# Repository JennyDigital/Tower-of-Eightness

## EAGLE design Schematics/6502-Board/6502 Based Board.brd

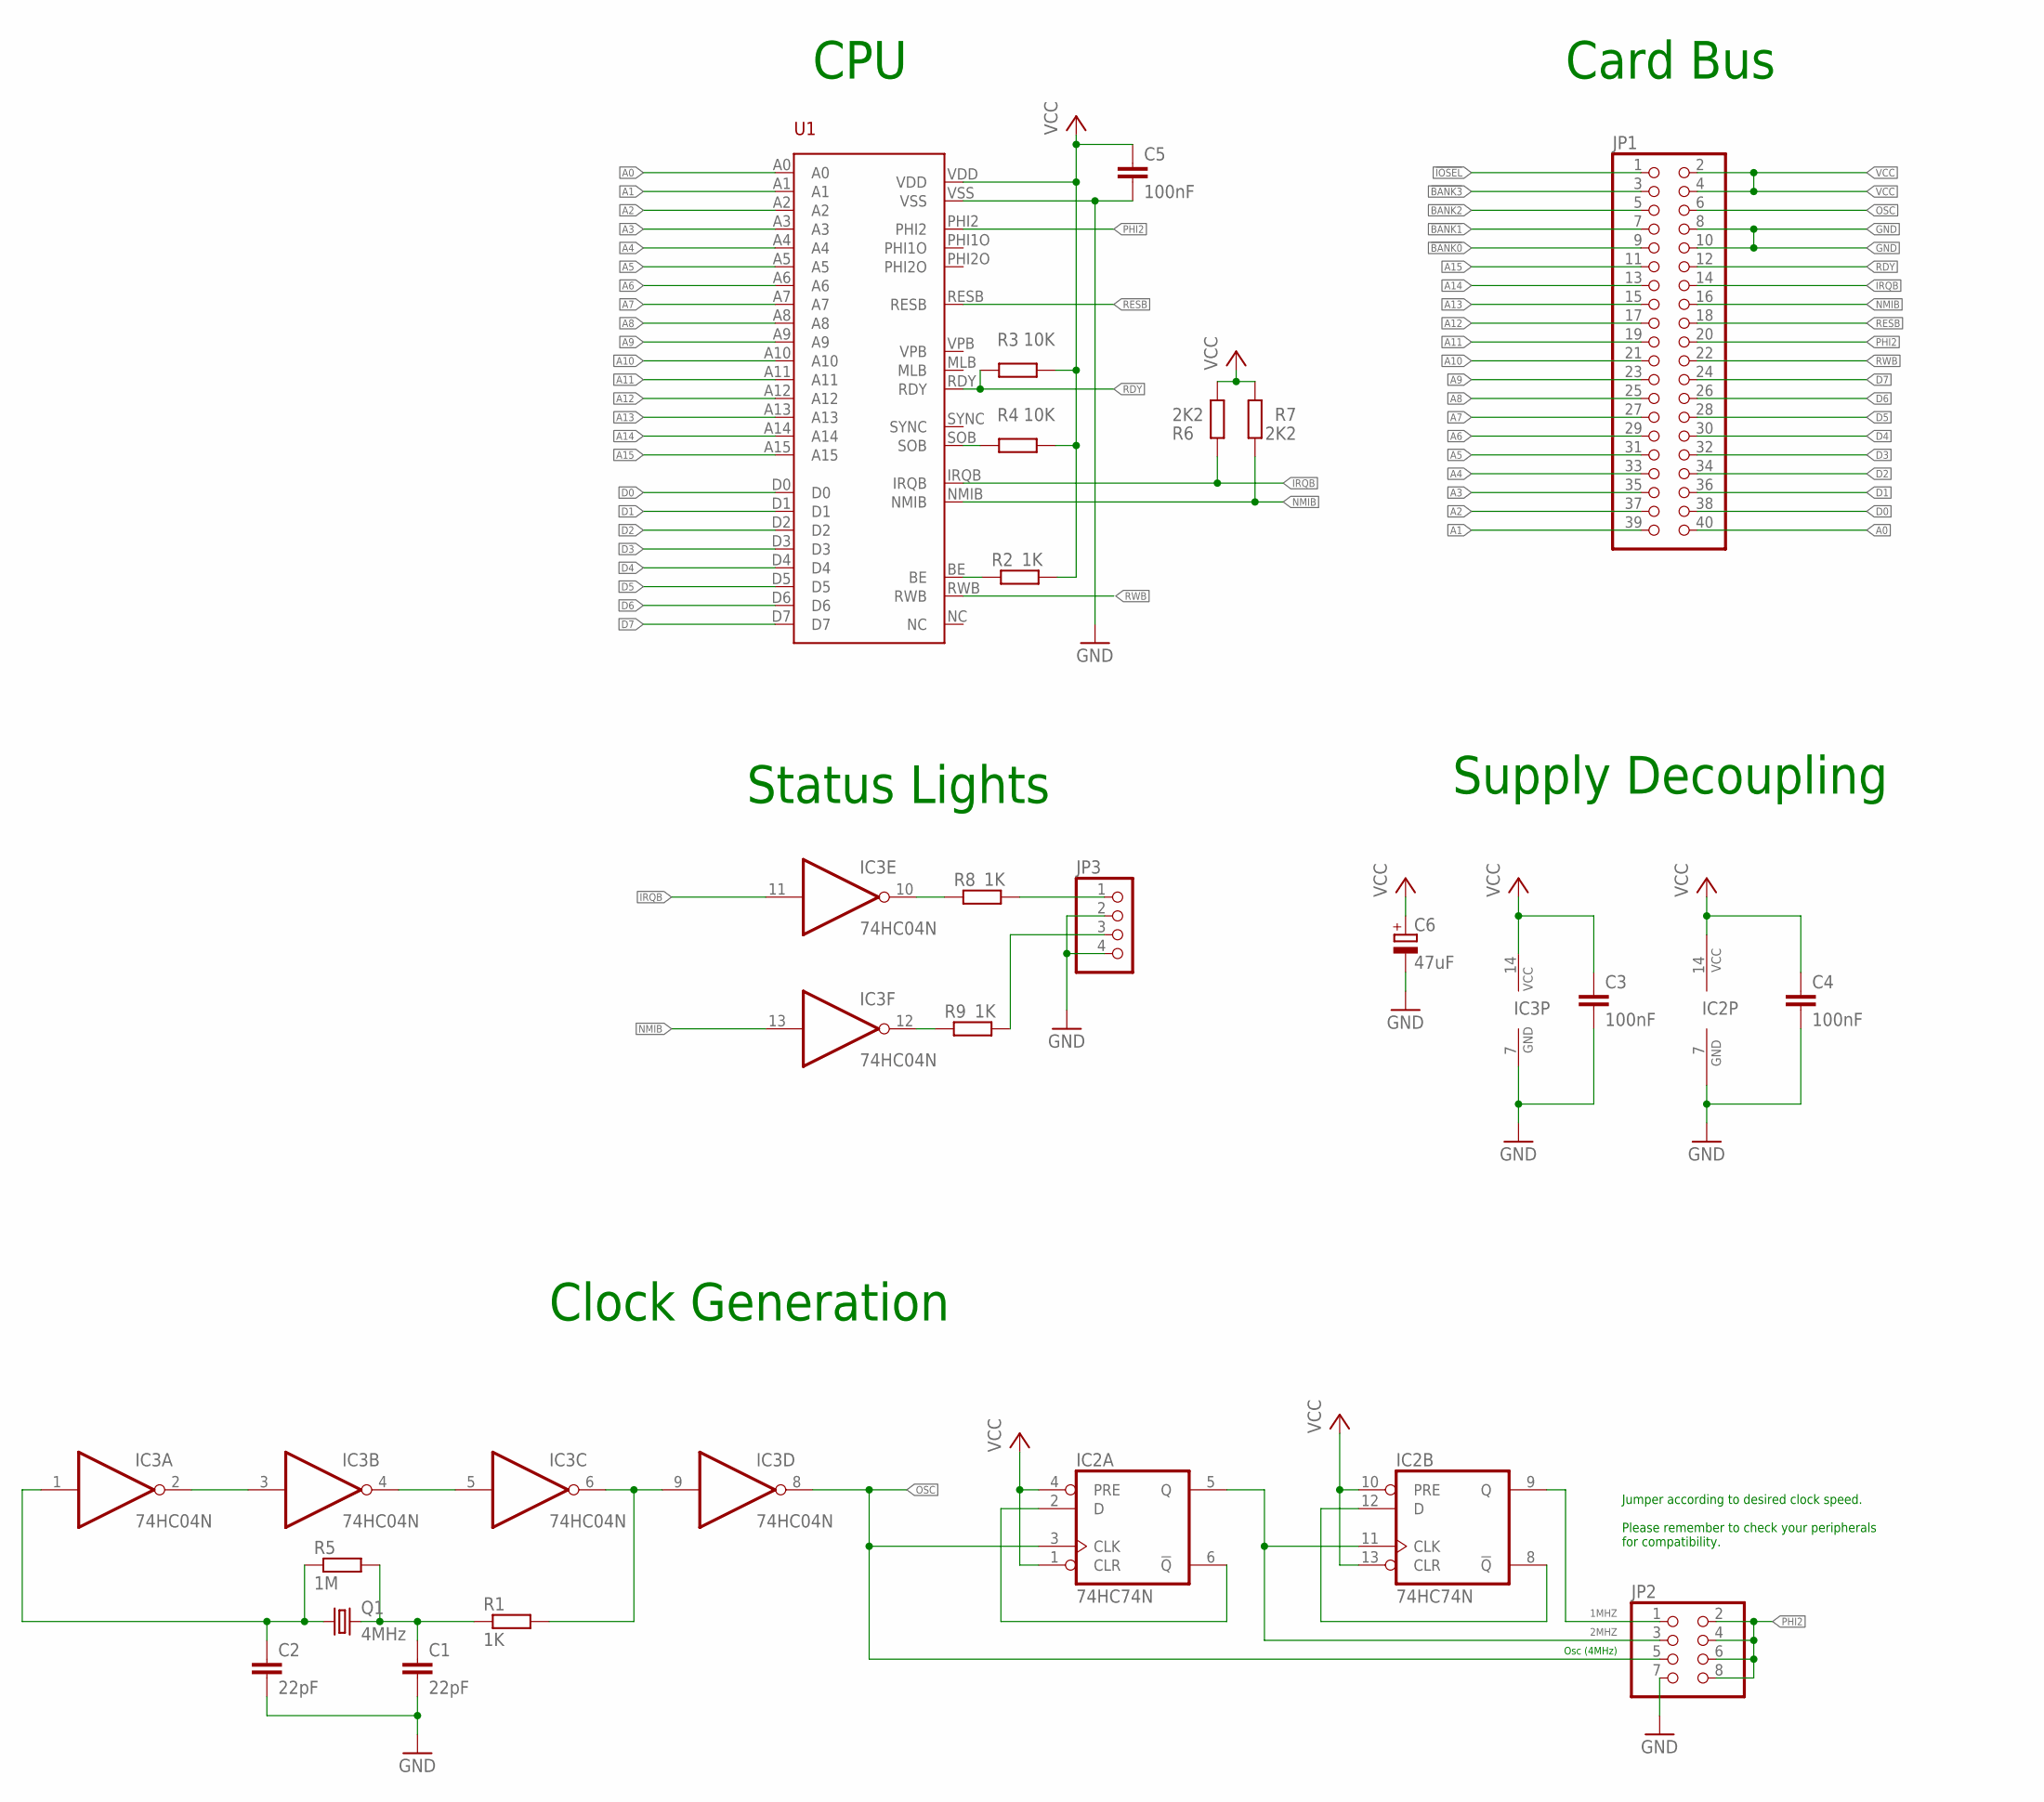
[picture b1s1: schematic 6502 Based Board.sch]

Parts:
C1, C2: 22pF; C050-025X075
C3, C4, C5: 100nF; C050-025X075
C6: 47uF; E2,5-7
IC2: 74HC74N; DIL14
IC3: 74HC04N; DIL14
JP1: PINHD-2X20/90; 2X20/90
JP2: PINHD-2X4; 2X04
JP3: PINHD-1X4/90; 1X04/90
Q1: 4MHz; HC49/S
R1, R2, R8, R9: 1K; 0207/2V
R3, R4: 10K; 0207/2V
R5: 1M; 0207/2V
R6, R7: 2K2; 0207/10
U1: W65C02S-DIP; DIP40

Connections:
1MHZ: IC2.9 (Q), JP2.1
2MHZ: IC2.5 (Q), IC2.11 (CLK), JP2.3
!BANK0: JP1.9
!BANK1: JP1.7
!BANK2: JP1.5
!BANK3: JP1.3
!IOSEL: JP1.1
A0: JP1.40, U1.A0
A1: JP1.39, U1.A1
A2: JP1.37, U1.A2
A3: JP1.35, U1.A3
A4: JP1.33, U1.A4
A5: JP1.31, U1.A5
A6: JP1.29, U1.A6
A7: JP1.27, U1.A7
A8: JP1.25, U1.A8
A9: JP1.23, U1.A9
A10: JP1.21, U1.A10
A11: JP1.19, U1.A11
A12: JP1.17, U1.A12
A13: JP1.15, U1.A13
A14: JP1.13, U1.A14
A15: JP1.11, U1.A15
D0: JP1.38, U1.D0
D1: JP1.36, U1.D1
D2: JP1.34, U1.D2
D3: JP1.32, U1.D3
D4: JP1.30, U1.D4
D5: JP1.28, U1.D5
D6: JP1.26, U1.D6
D7: JP1.24, U1.D7
GND: C1.2, C2.2, C3.2, C4.2, C5.2, C6.-, IC2.7 (GND), IC3.7 (GND), JP1.8, JP1.10, JP2.7, JP3.2, JP3.4, U1.VSS
IRQB: IC3.11 (I), JP1.14, R6.1, U1.IRQB
IRQ_LED: JP3.1, R8.2
unnamed: IC2.2 (D), IC2.6 (!Q)
unnamed: IC3.4 (O), IC3.5 (I)
unnamed: IC3.6 (O), IC3.9 (I), R1.2
unnamed: C1.1, Q1.2, R1.1, R5.2
unnamed: C2.1, IC3.1 (I), Q1.1, R5.1
unnamed: IC3.2 (O), IC3.3 (I)
unnamed: IC2.8 (!Q), IC2.12 (D)
unnamed: IC3.10 (O), R8.1
unnamed: IC3.12 (O), R9.1
unnamed: R2.1, U1.BE
unnamed: R4.1, U1.SOB
NMIB: IC3.13 (I), JP1.16, R7.1, U1.NMIB
NMI_LED: JP3.3, R9.2
OSC: IC2.3 (CLK), IC3.8 (O), JP1.6, JP2.5
PHI2: JP1.20, JP2.2, JP2.4, JP2.6, JP2.8, U1.PHI2
RDY: JP1.12, R3.1, U1.RDY
RESB: JP1.18, U1.RESB
RWB: JP1.22, U1.RWB
VCC: C3.1, C4.1, C5.1, C6.+, IC2.1 (CLR), IC2.4 (PRE), IC2.10 (PRE), IC2.13 (CLR), IC2.14 (VCC), IC3.14 (VCC), JP1.2, JP1.4, R2.2, R3.2, R4.2, R6.2, R7.2, U1.VDD

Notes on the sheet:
CPU
Clock Generation
Card Bus
Status Lights
Supply Decoupling
Jumper according to desired clock speed. Please remember to check your peripherals for compatibility.
Osc (4MHz)

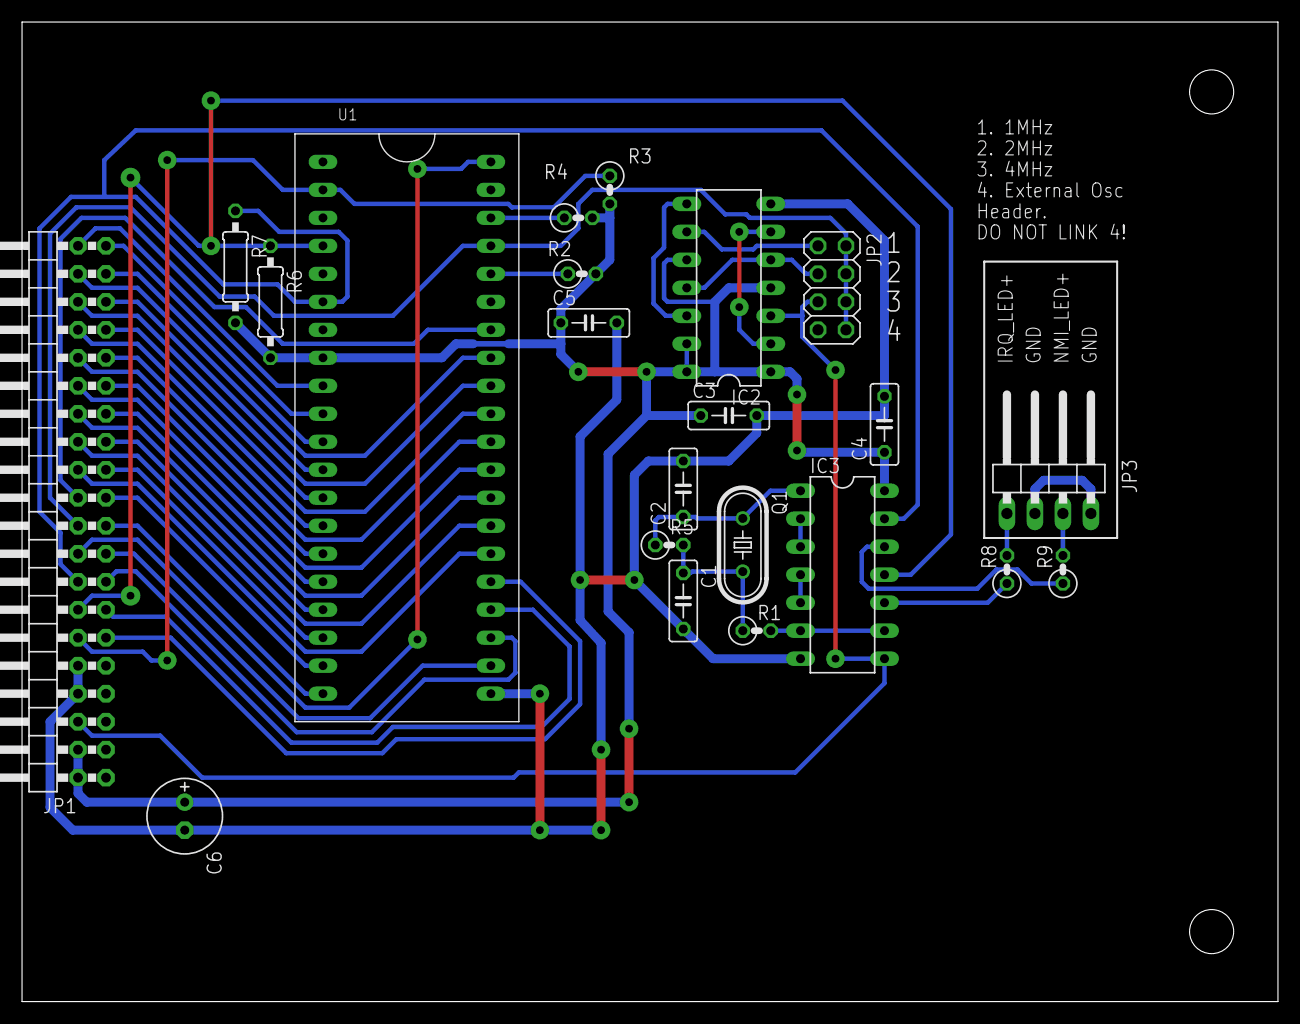
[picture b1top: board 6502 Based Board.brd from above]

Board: 2 copper layers, 114.0 x 88.9 mm, 22 parts (0 on the bottom side), 48 nets.

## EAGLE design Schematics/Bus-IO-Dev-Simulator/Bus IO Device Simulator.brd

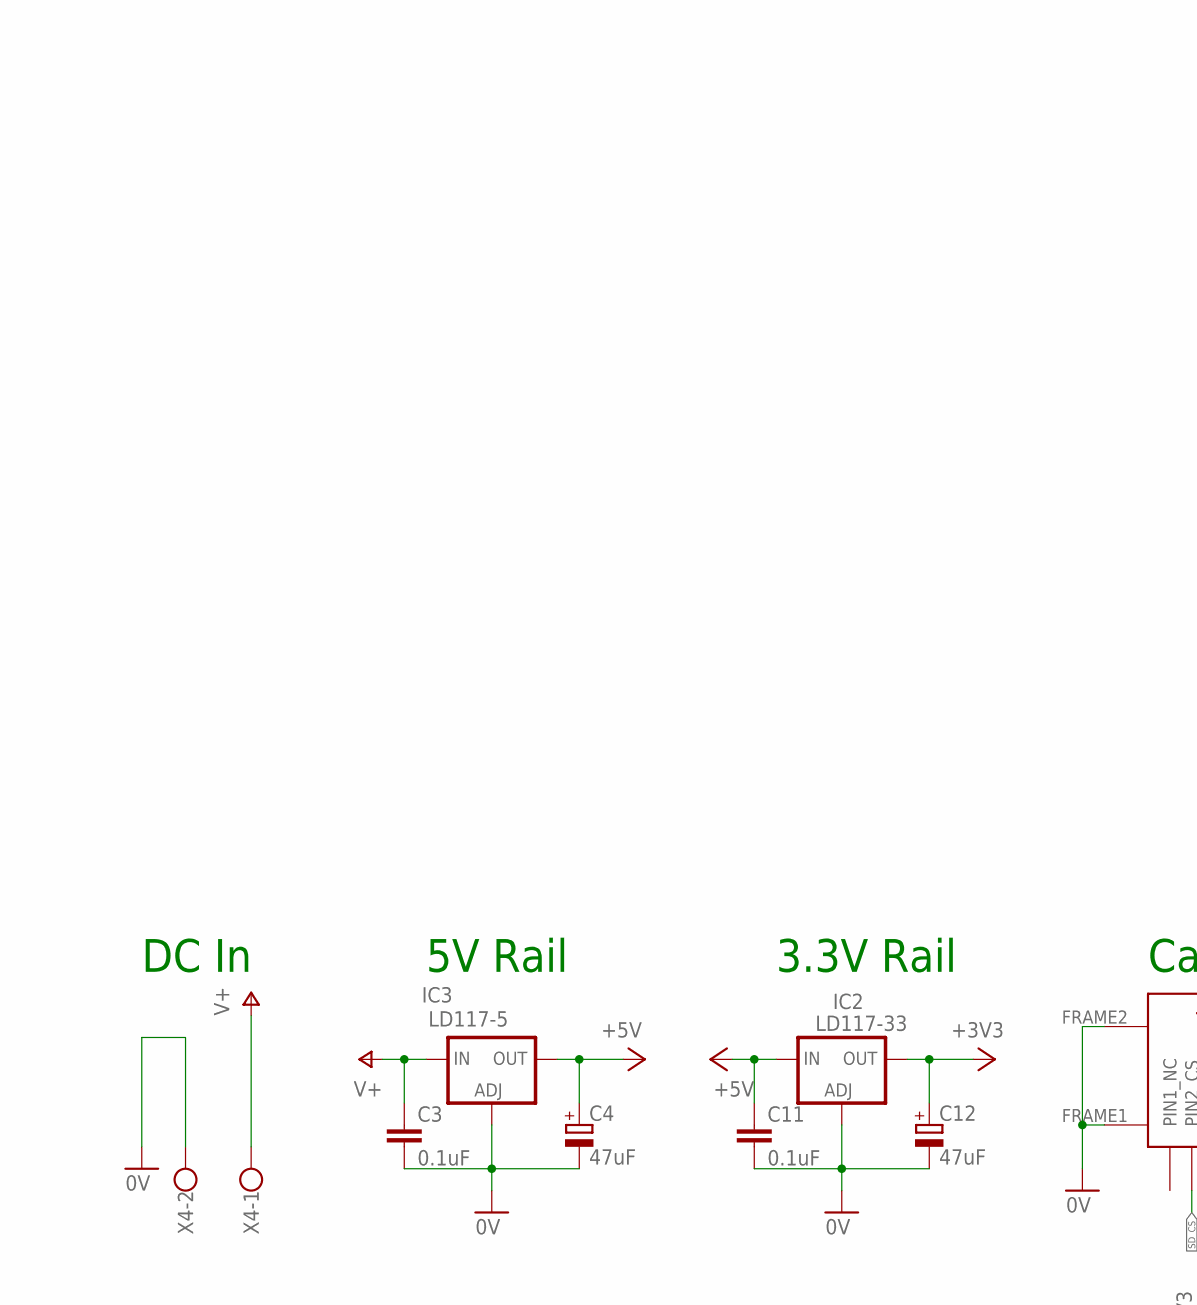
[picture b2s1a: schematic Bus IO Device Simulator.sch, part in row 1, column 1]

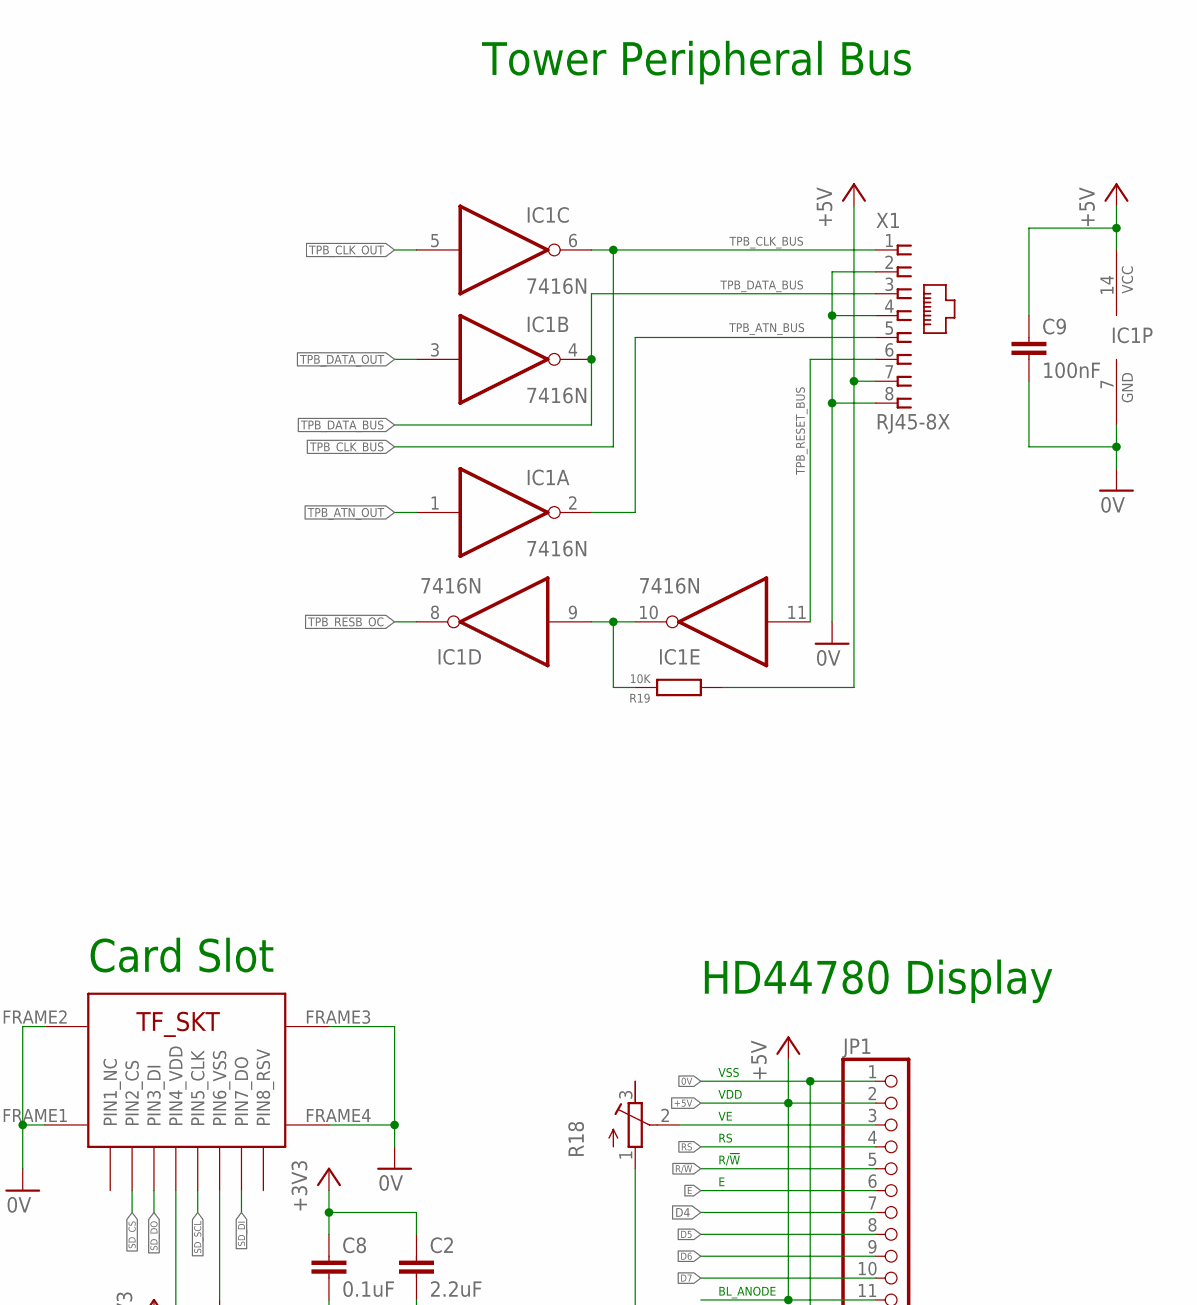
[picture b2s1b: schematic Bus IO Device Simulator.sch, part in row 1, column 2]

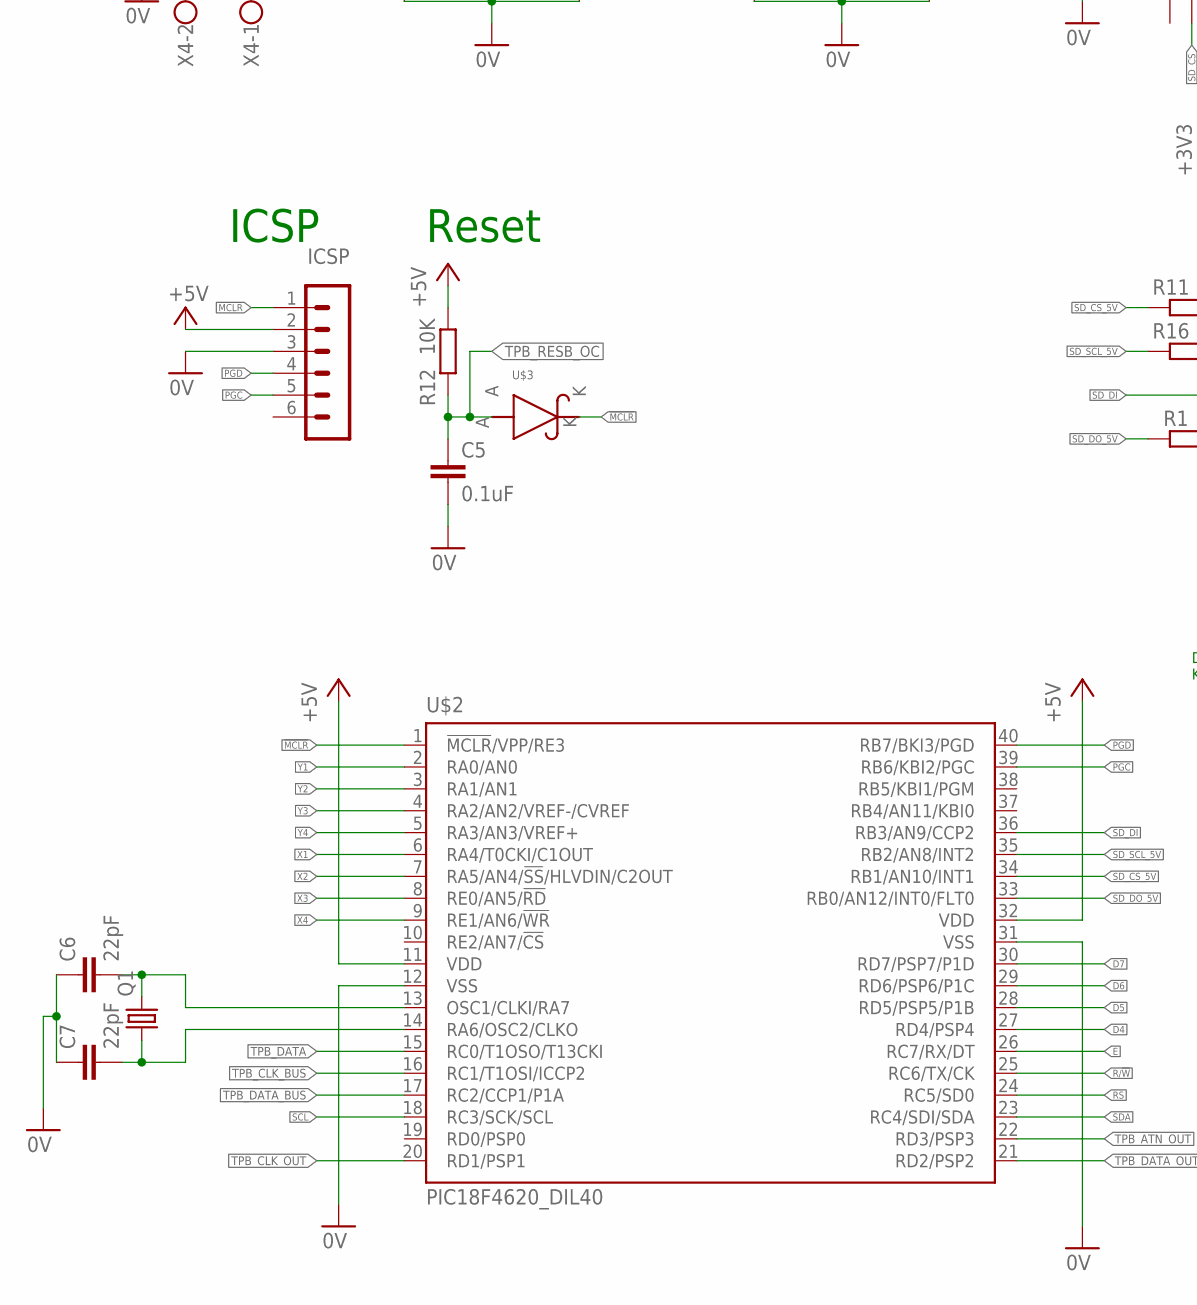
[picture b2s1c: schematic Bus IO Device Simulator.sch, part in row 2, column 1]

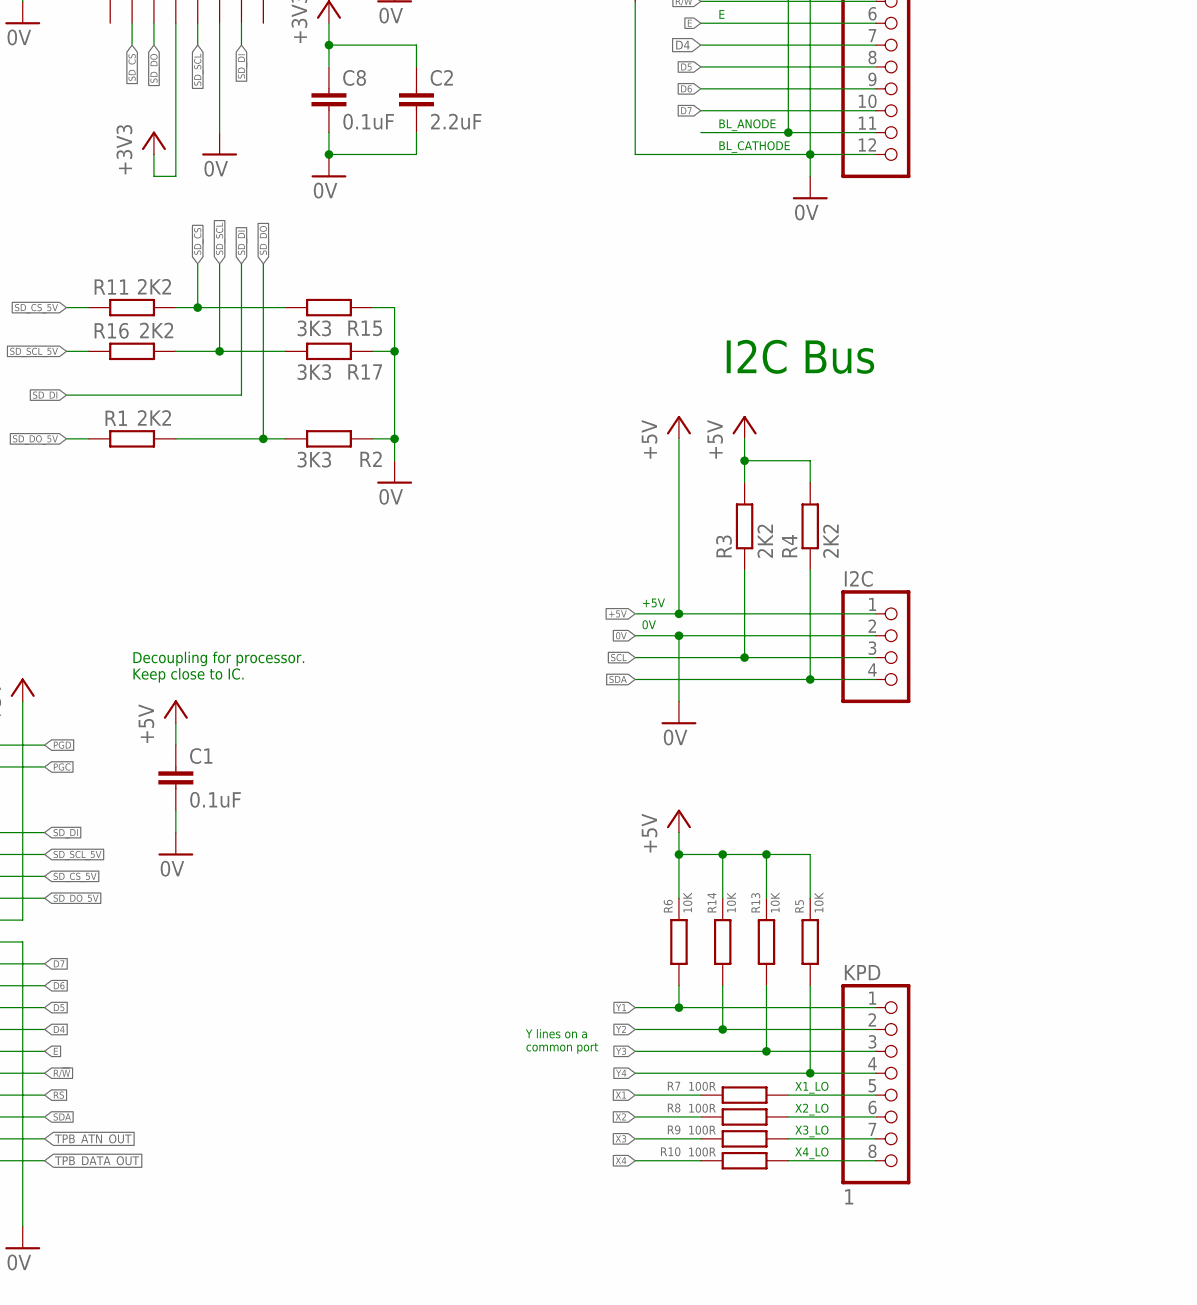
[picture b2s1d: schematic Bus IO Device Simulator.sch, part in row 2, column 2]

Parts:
C1, C3, C5, C8, C11: 0.1uF; C0603
C2: 2.2uF; C1206
C4, C12: 47uF; SMC_D
C6, C7: 22pF; C0603
C9: 100nF; C050-025X075
I2C: PINHD-1X4; 1X04
IC1: 7416N; DIL14
IC2: LD117-33; SOT223
IC3: LD117-5; SOT223
ICSP: MA06-1
JP1: PINHD-1X12; 1X12
KPD: 1; 1X08
Q1: CRYSTALHC49U-V; HC49U-V
R1, R3, R4, R11, R16: 2K2; R0603
R2, R15, R17: 3K3; R0603
R5, R6, R12, R13, R14, R19: 10K; R0603
R7, R8, R9, R10: 100R; R0603
R18: R-TRIMM64W; RTRIM64W
U$1: TF_SKT; CLIP_DOWN
U$2: PIC18F4620_DIL40; DIL40
U$3: ZHCS750; SOT23
X1: RJ45-8X; RJ45-NO-SHIELD
X4: W237-102; MPN 237-102

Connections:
0V: C1.2, C2.2, C3.2, C4.-, C5.2, C6.1, C7.1, C8.2, C9.2, C11.2, C12.-, I2C.2, IC1.7 (GND), IC2.1 (ADJ), IC3.1 (ADJ), ICSP.3, JP1.1, JP1.12, R2.1, R15.1, R17.1, R18.1 (E), U$1.FRAME1, U$1.FRAME2, U$1.FRAME3, U$1.FRAME4, U$1.PIN6_VSS, U$2.12 (VSS), U$2.31 (VSS), X1.2, X1.4, X1.8, X4.2
!MCLR: ICSP.1, U$2.1 (!MCLR!/VPP/RE3), U$3.K
+3V3: C2.1, C8.1, C12.+, IC2.4 (OUT), U$1.PIN4_VDD
+5V: C1.1, C4.+, C9.1, C11.1, I2C.1, IC1.14 (VCC), IC2.3 (IN), IC3.4 (OUT), ICSP.2, JP1.2, JP1.11, R3.2, R4.2, R5.2, R6.2, R12.2, R13.2, R14.2, R19.1, U$2.11 (VDD), U$2.32 (VDD), X1.7
D4: JP1.7, U$2.27 (RD4/PSP4)
D5: JP1.8, U$2.28 (RD5/PSP5/P1B)
D6: JP1.9, U$2.29 (RD6/PSP6/P1C)
D7: JP1.10, U$2.30 (RD7/PSP7/P1D)
E: JP1.6, U$2.26 (RC7/RX/DT)
unnamed: C6.2, Q1.2, U$2.13 (OSC1/CLKI/RA7)
unnamed: C7.2, Q1.1, U$2.14 (RA6/OSC2/CLKO)
unnamed: JP1.3, R18.2 (S)
unnamed: IC1.9 (I), IC1.10 (O), R19.2
PGC: ICSP.5, U$2.39 (RB6/KBI2/PGC)
PGD: ICSP.4, U$2.40 (RB7/BKI3/PGD)
R/!W: JP1.5, U$2.25 (RC6/TX/CK)
RS: JP1.4, U$2.24 (RC5/SD0)
SCL: I2C.3, R3.1, U$2.18 (RC3/SCK/SCL)
SDA: I2C.4, R4.1, U$2.23 (RC4/SDI/SDA)
SD_CS: R11.1, R15.2, U$1.PIN2_CS
SD_CS_5V: R11.2, U$2.34 (RB1/AN10/INT1)
SD_DI: U$1.PIN7_DO, U$2.36 (RB3/AN9/CCP2)
SD_DO: R1.1, R2.2, U$1.PIN3_DI
SD_DO_5V: R1.2, U$2.33 (RB0/AN12/INT0/FLT0)
SD_SCL: R16.1, R17.2, U$1.PIN5_CLK
SD_SCL_5V: R16.2, U$2.35 (RB2/AN8/INT2)
TPB_ATN_BUS: IC1.2 (O), X1.5
TPB_ATN_OUT: IC1.1 (I), U$2.22 (RD3/PSP3)
TPB_CLK_BUS: IC1.6 (O), U$2.16 (RC1/T1OSI/ICCP2), X1.1
TPB_CLK_OUT: IC1.5 (I), U$2.20 (RD1/PSP1)
TPB_DATA: U$2.15 (RC0/T1OSO/T13CKI)
TPB_DATA_BUS: IC1.4 (O), U$2.17 (RC2/CCP1/P1A), X1.3
TPB_DATA_OUT: IC1.3 (I), U$2.21 (RD2/PSP2)
TPB_RESB_OC: C5.1, IC1.8 (O), R12.1, U$3.A
TPB_RESET_BUS: IC1.11 (I), X1.6
V+: C3.1, IC3.3 (IN), X4.1
X1: R7.2, U$2.6 (RA4/T0CKI/C1OUT)
X1_LO: KPD.5, R7.1
X2: R8.2, U$2.7 (RA5/AN4/!SS!/HLVDIN/C2OUT)
X2_LO: KPD.6, R8.1
X3: R9.2, U$2.8 (RE0/AN5/!RD)
X3_LO: KPD.7, R9.1
X4: R10.2, U$2.9 (RE1/AN6/!WR)
X4_LO: KPD.8, R10.1
Y1: KPD.1, R6.1, U$2.2 (RA0/AN0)
Y2: KPD.2, R14.1, U$2.3 (RA1/AN1)
Y3: KPD.3, R13.1, U$2.4 (RA2/AN2/VREF-/CVREF)
Y4: KPD.4, R5.1, U$2.5 (RA3/AN3/VREF+)

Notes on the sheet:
5V Rail
DC In
Reset
Card Slot
3.3V Rail
Decoupling for processor. Keep close to IC.
HD44780 Display
VSS
VDD
R/!W
BL_ANODE
BL_CATHODE
ICSP
I2C Bus
+5V
X1_LO
X2_LO
X3_LO
X4_LO
Y lines on a common port
Tower Peripheral Bus

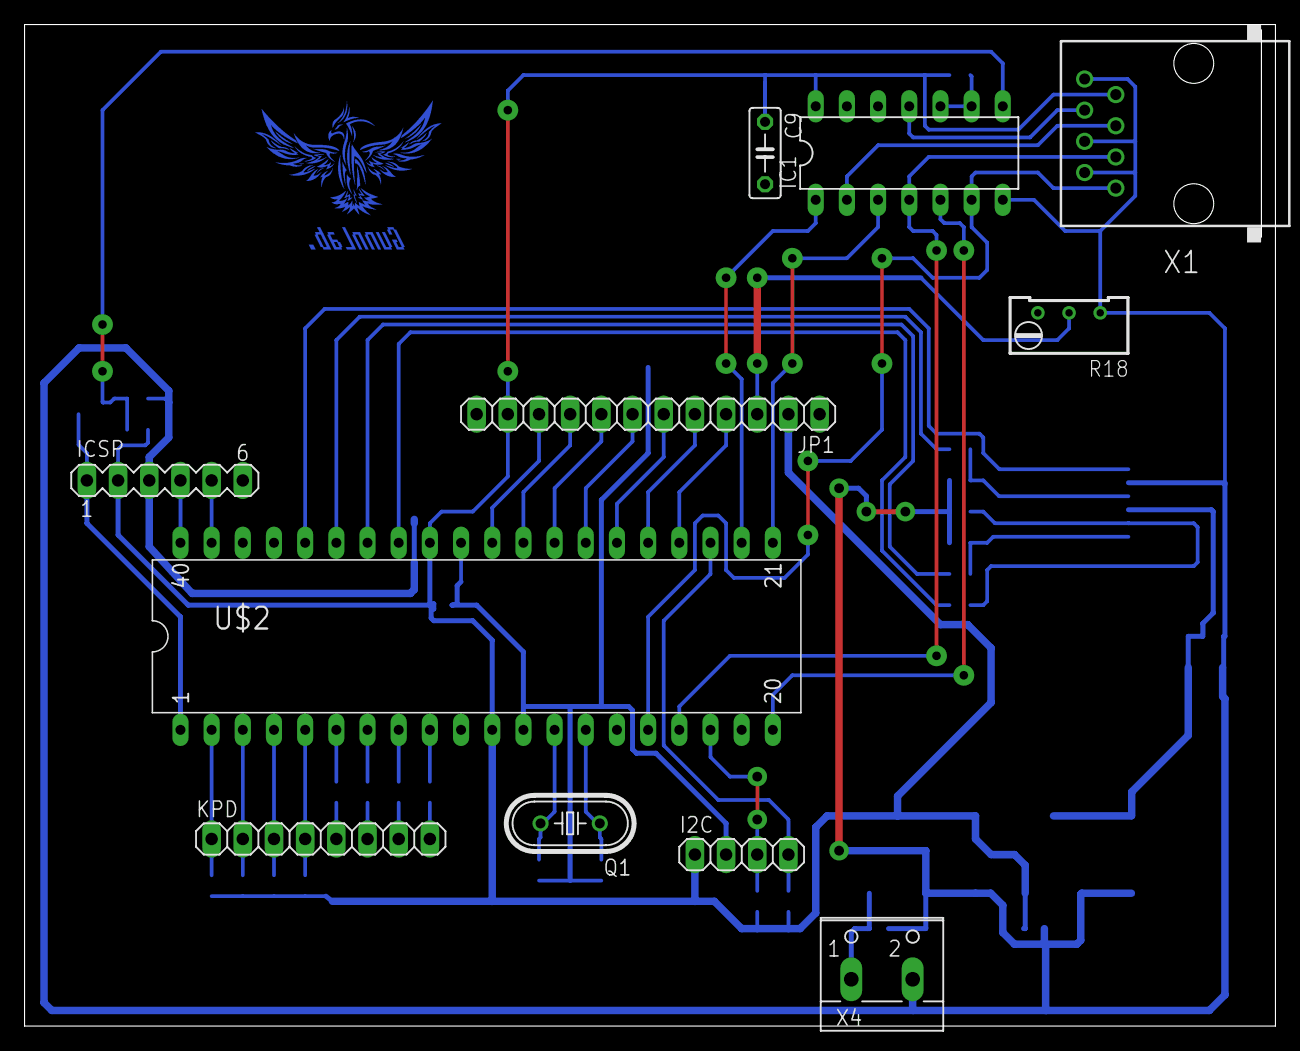
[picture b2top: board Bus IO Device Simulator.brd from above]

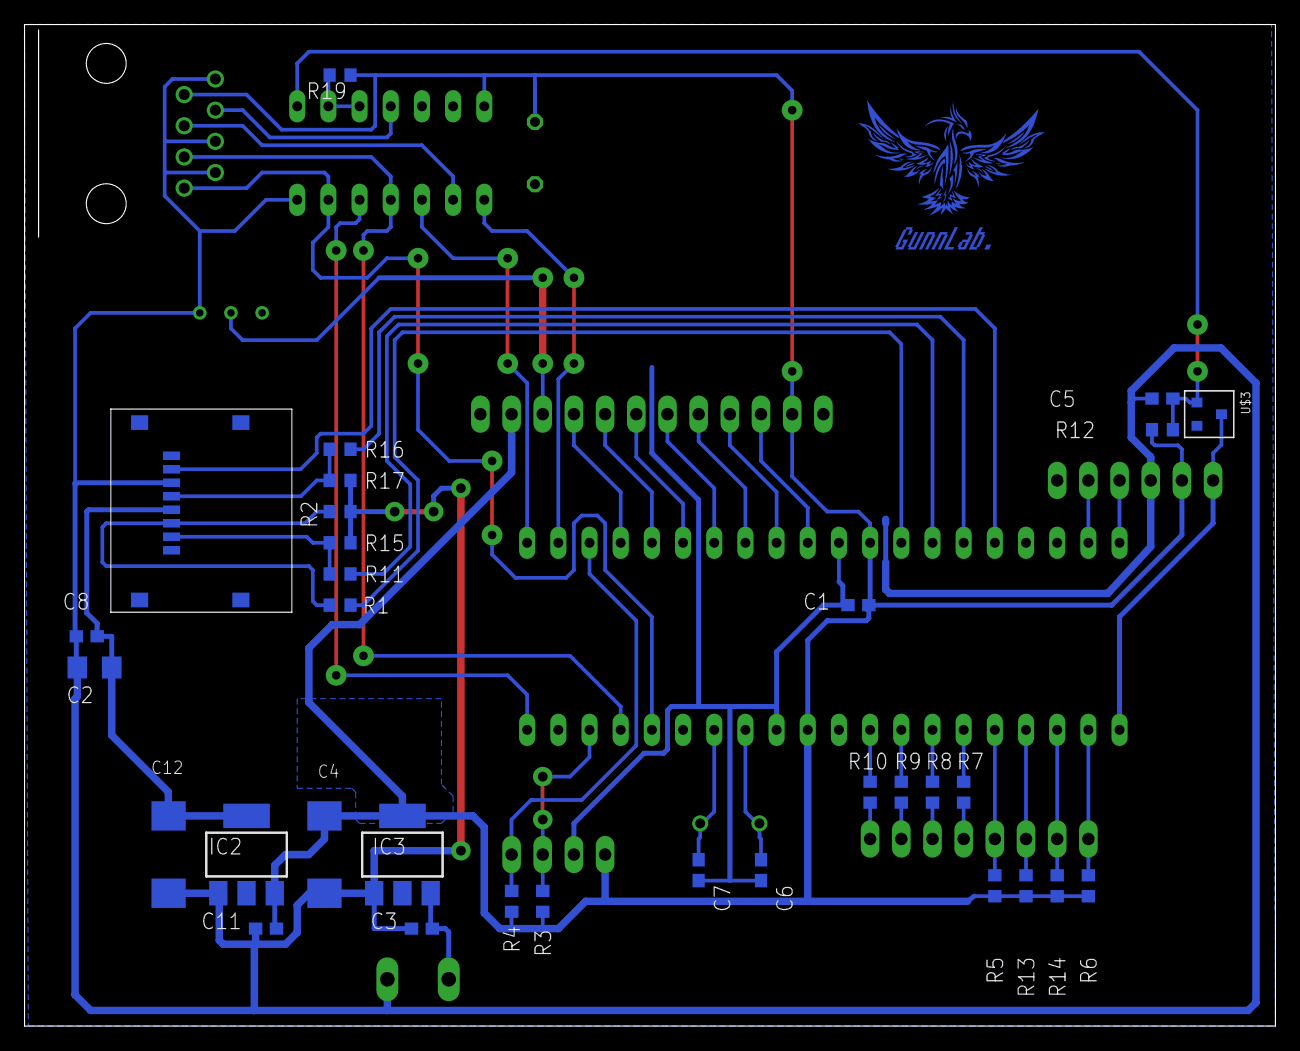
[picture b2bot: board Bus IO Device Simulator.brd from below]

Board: 2 copper layers, 101.9 x 81.6 mm, 44 parts (32 on the bottom side), 47 nets.

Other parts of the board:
U$4: LIONTECH

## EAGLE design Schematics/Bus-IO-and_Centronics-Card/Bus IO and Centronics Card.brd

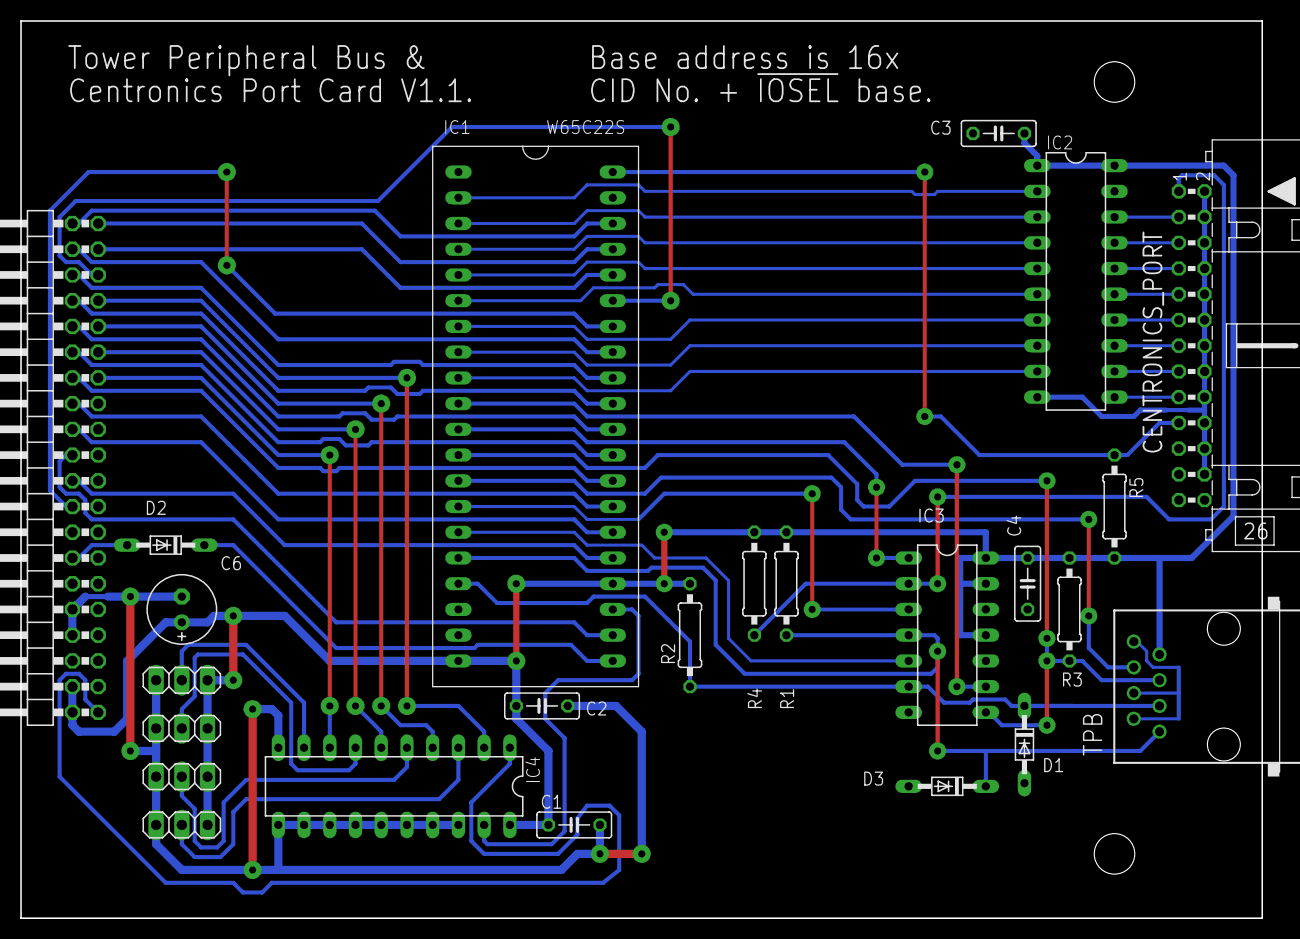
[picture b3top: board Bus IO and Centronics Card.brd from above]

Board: 2 copper layers, 124.3 x 88.6 mm, 24 parts (0 on the bottom side), 55 nets.

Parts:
C1, C2, C3, C4: 100nF; C050-025X075
C6: 47uF; E2,5-7
CENTRONICS_PORT: P1; ML26L
D1, D2, D3: BAT85; DO34-7
IC1: W65C22S; W65C22-DIP
IC2: 74LS245N; DIL20
IC3: 7416N; DIL14
IC4: 74688N; DIL20
JP1: SYSBUS; 2X20/90
JP2: CID0; 1X03
JP3: CID1; 1X03
JP4: CID2; 1X03
JP5: CID3; 1X03
R1, R2, R3, R4, R5: 4K7; 0207/10
TPB: RJ45-8X; RJ45-NO-SHIELD

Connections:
!IOSEL: IC4.1, JP1.1
!VIA_SEL: IC1.CS2B, IC4.19
A0: IC1.RS0, JP1.40
A1: IC1.RS1, JP1.39
A2: IC1.RS2, JP1.37
A3: IC1.RS3, JP1.35
A4: IC4.2, JP1.33
A5: IC4.4, JP1.31
A6: IC4.6, JP1.29
A7: IC4.8, JP1.27
CA1_ACK: CENTRONICS_PORT.19, IC1.CA1, R5.1
CID0: IC4.3, JP2.2
CID1: IC4.5, JP3.2
CID2: IC4.7, JP4.2
CID3: IC4.9, JP5.2
D0: IC1.D0, JP1.38
D1: IC1.D1, JP1.36
D2: IC1.D2, JP1.34
D3: IC1.D3, JP1.32
D4: IC1.D4, JP1.30
D5: IC1.D5, JP1.28
D6: IC1.D6, JP1.26
D7: IC1.D7, JP1.24
GND: C1.2, C2.2, C3.2, C4.2, C6.-, CENTRONICS_PORT.2, CENTRONICS_PORT.4, CENTRONICS_PORT.6, CENTRONICS_PORT.8, CENTRONICS_PORT.10, CENTRONICS_PORT.12, CENTRONICS_PORT.14, CENTRONICS_PORT.16, CENTRONICS_PORT.18, CENTRONICS_PORT.20, CENTRONICS_PORT.22, CENTRONICS_PORT.24, D1.A, D3.A, IC1.VSS, IC2.10, IC2.19, IC3.7, IC4.10, IC4.11, IC4.12, IC4.13, IC4.14, IC4.15, IC4.16, IC4.17, IC4.18, JP1.8, JP1.10, JP2.3, JP3.3, JP4.3, JP5.3, TPB.2, TPB.4, TPB.8
IRQB: D2.C, IC1.IRQB
unnamed: D2.A, JP1.14
PA0: IC1.PA0, IC2.2
PA1: IC1.PA1, IC2.3
PA2: IC1.PA2, IC2.4
PA3: IC1.PA3, IC2.5
PA4: IC1.PA4, IC2.6
PA5: IC1.PA5, IC2.7
PA6: IC1.PA6, IC2.8
PA7: IC1.PA7, IC2.9
PB0_ATN_OUT: IC1.PB0, IC3.9
PB1_STROBE: IC1.PB1, IC3.1
PB2_TPB_ATN: IC1.PB2, IC3.8, R3.1, TPB.5
PB3_TPB_SELECT: IC1.PB3, TPB.6
PB4_TPB_CLK: IC1.PB4, IC3.3
PB5_TPB_DATA: IC1.PB5, IC3.5
PB6_TPB_CLK: D3.C, IC1.PB6, IC3.4, R1.1, TPB.1
PB7_TPB_DATA: D1.C, IC1.PB7, IC3.6, R2.1, TPB.3
PD0: CENTRONICS_PORT.3, IC2.18
PD1: CENTRONICS_PORT.5, IC2.17
PD2: CENTRONICS_PORT.7, IC2.16
PD3: CENTRONICS_PORT.9, IC2.15
PD4: CENTRONICS_PORT.11, IC2.14
PD5: CENTRONICS_PORT.13, IC2.13
PD6: CENTRONICS_PORT.15, IC2.12
PD7: CENTRONICS_PORT.17, IC2.11
PHI2: IC1.PHI2, JP1.20
RESB: IC1.RESB, JP1.18
RWB: IC1.RWB, JP1.22
STROBE: CENTRONICS_PORT.1, IC3.2, R4.1
VCC: C1.1, C2.1, C3.1, C4.1, C6.+, IC1.CS1, IC1.VDD, IC2.1, IC2.20, IC3.11, IC3.13, IC3.14, IC4.20, JP1.2, JP1.4, JP2.1, JP3.1, JP4.1, JP5.1, R1.2, R2.2, R3.2, R4.2, R5.2, TPB.7

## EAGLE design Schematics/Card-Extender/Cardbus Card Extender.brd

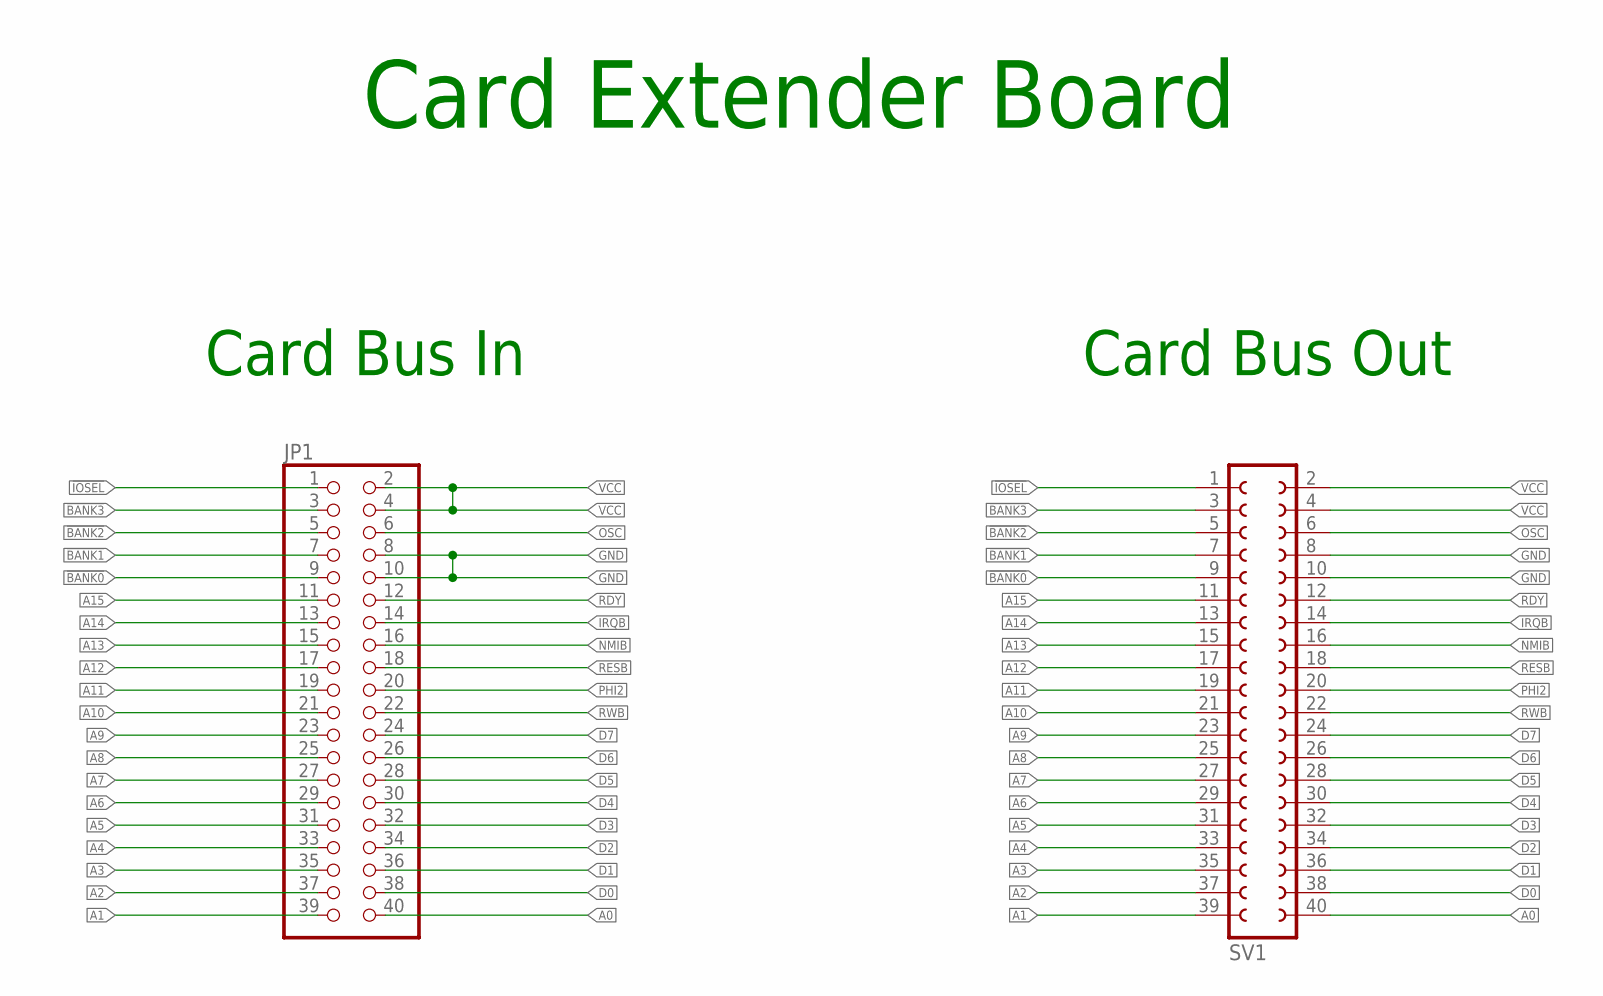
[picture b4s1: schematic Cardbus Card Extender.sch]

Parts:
JP1: PINHD-2X20/90; 2X20/90
SV1: FE20-2W

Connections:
!BANK0: JP1.9, SV1.9
!BANK1: JP1.7, SV1.7
!BANK2: JP1.5, SV1.5
!BANK3: JP1.3, SV1.3
!IOSEL: JP1.1, SV1.1
A0: JP1.40, SV1.40
A1: JP1.39, SV1.39
A2: JP1.37, SV1.37
A3: JP1.35, SV1.35
A4: JP1.33, SV1.33
A5: JP1.31, SV1.31
A6: JP1.29, SV1.29
A7: JP1.27, SV1.27
A8: JP1.25, SV1.25
A9: JP1.23, SV1.23
A10: JP1.21, SV1.21
A11: JP1.19, SV1.19
A12: JP1.17, SV1.17
A13: JP1.15, SV1.15
A14: JP1.13, SV1.13
A15: JP1.11, SV1.11
D0: JP1.38, SV1.38
D1: JP1.36, SV1.36
D2: JP1.34, SV1.34
D3: JP1.32, SV1.32
D4: JP1.30, SV1.30
D5: JP1.28, SV1.28
D6: JP1.26, SV1.26
D7: JP1.24, SV1.24
GND: JP1.8, JP1.10, SV1.8, SV1.10
IRQB: JP1.14, SV1.14
NMIB: JP1.16, SV1.16
OSC: JP1.6, SV1.6
PHI2: JP1.20, SV1.20
RDY: JP1.12, SV1.12
RESB: JP1.18, SV1.18
RWB: JP1.22, SV1.22
VCC: JP1.2, JP1.4, SV1.2, SV1.4

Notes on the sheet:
Card Bus In
Card Bus Out
Card Extender Board

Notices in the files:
parts and their libraries:
con-headers-jp: Copyright (C) 2008, Bob Starr
